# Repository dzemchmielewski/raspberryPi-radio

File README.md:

Radio for playing internet streams, with knobs, buttons, LEDs and OLED display

./software - python code
./kicad - kicad files for schematic, PCB and plexi cut out

 dzem 2024

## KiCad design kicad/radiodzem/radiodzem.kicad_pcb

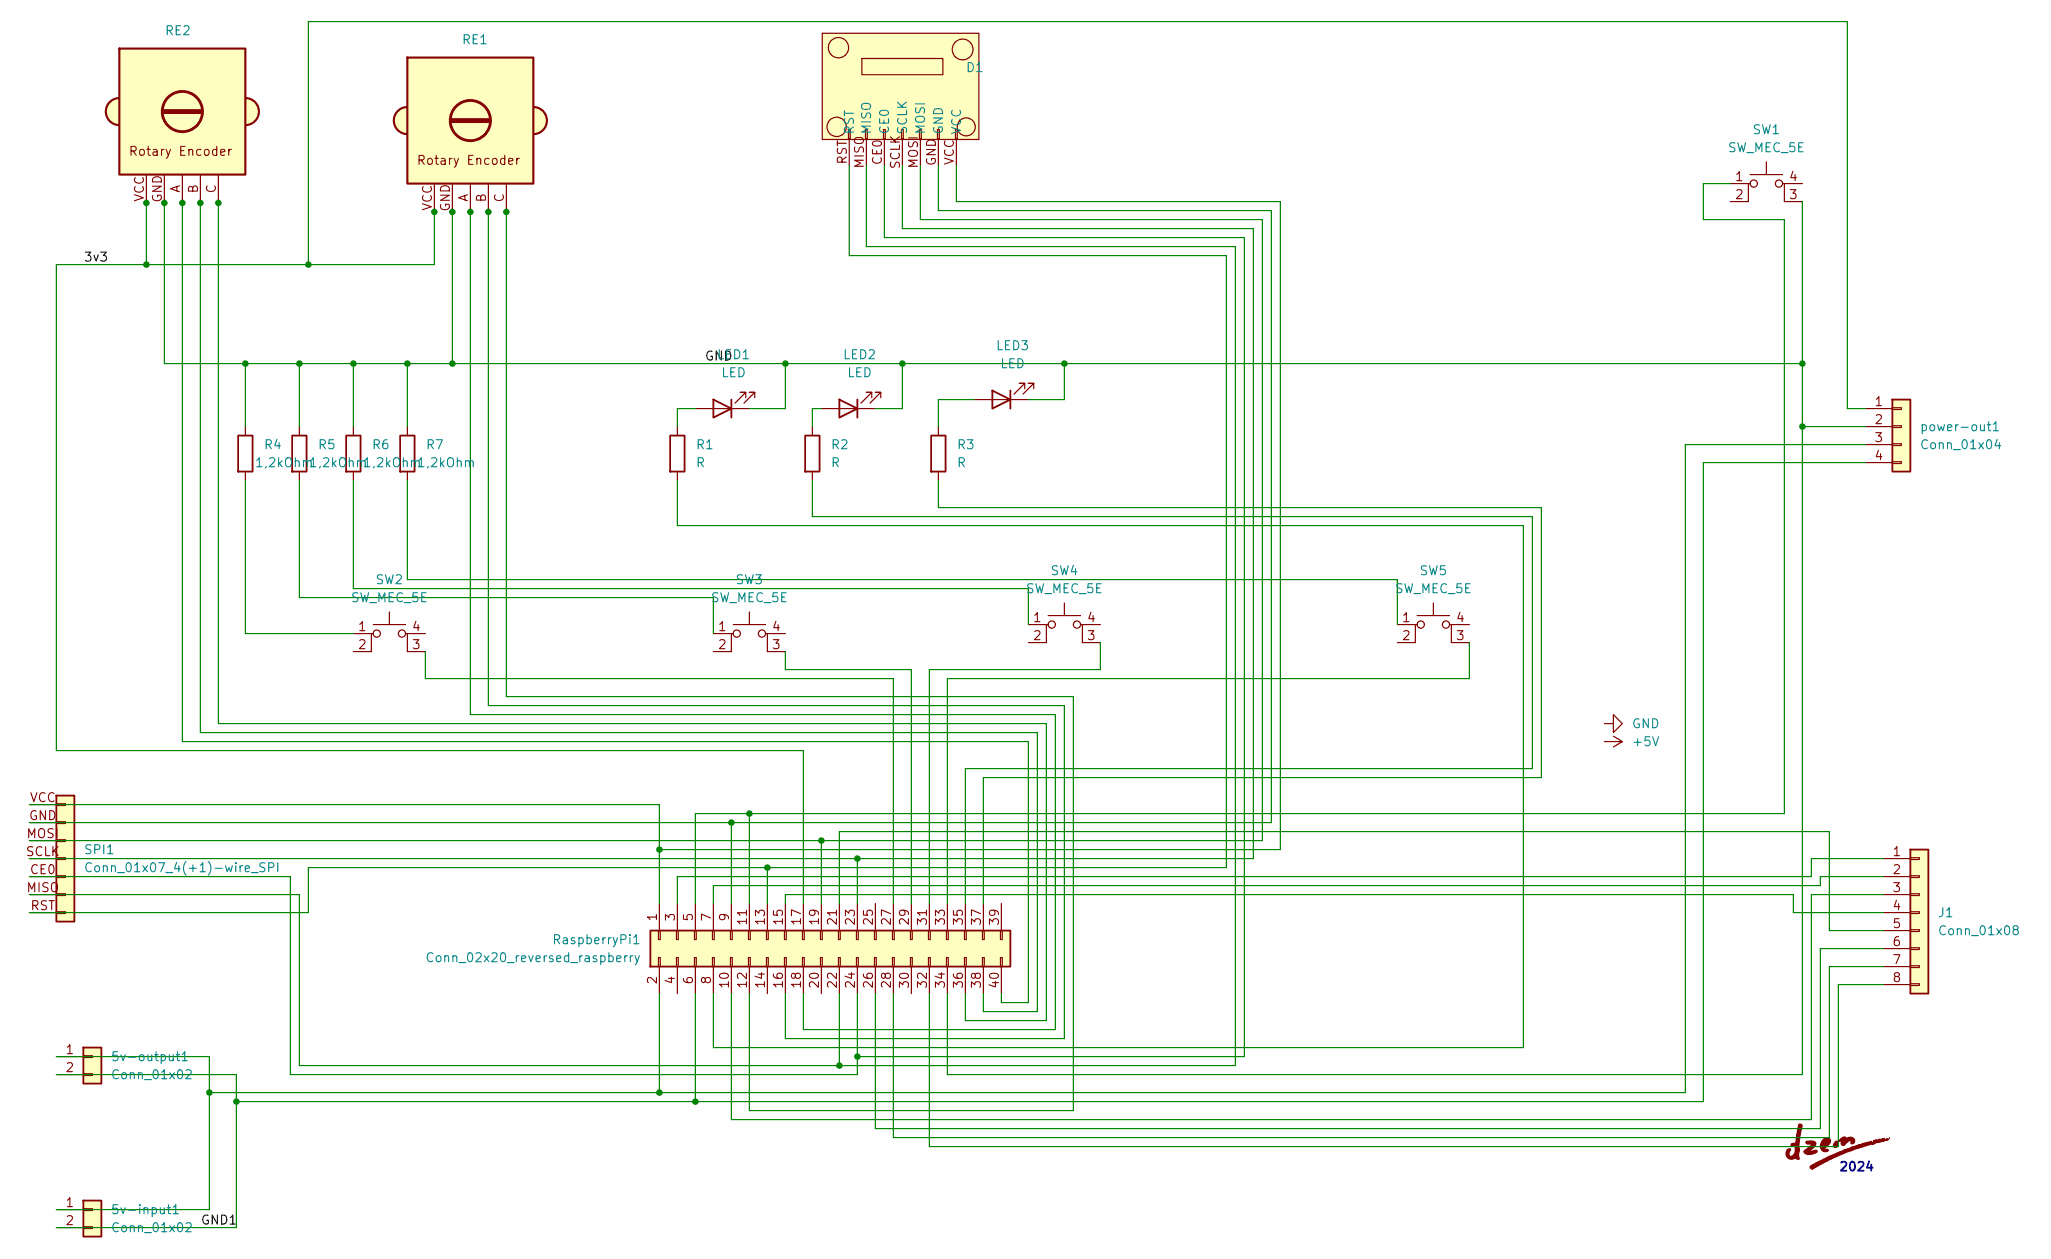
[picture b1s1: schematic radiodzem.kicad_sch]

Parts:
5v-input1: Conn_01x02; SolderWire-1sqmm_1x02_P5.4mm_D1.4mm_OD2.7mm
5v-output1: Conn_01x02; PinHeader_1x02_P2.54mm_Vertical
D1: Waveshare 1.32inch OLED Display Module
J1: Conn_01x08; PinHeader_1x08_P2.54mm_Vertical
LED1, LED2, LED3: LED; LED_D3.0mm
R1, R2, R3: R; R_Axial_DIN0207_L6.3mm_D2.5mm_P7.62mm_Horizontal
R4, R5, R6, R7: 1,2kOhm; R_Axial_DIN0207_L6.3mm_D2.5mm_P7.62mm_Horizontal
RE1, RE2: EC11 Rotary Encoder
RaspberryPi1: Conn_02x20_reversed_raspberry; PinHeader_RaspberryPi_reversed
SPI1: Conn_01x07_4(+1)-wire_SPI; PinHeader_1x07_P2.54mm_4(+1)-wire_SPI
SW1, SW2, SW3, SW4, SW5: SW_MEC_5E; SW_PUSH-12mm
power-out1: Conn_01x04; 4-pins_power_connector

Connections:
/3v3: RE1.VCC, RE2.VCC, RaspberryPi1.17, power-out1.1
/GND1: 5v-input1.2, 5v-output1.2, RaspberryPi1.6, power-out1.4
GND: LED1.1 (K), LED2.1 (K), LED3.1 (K), R4.1, R5.1, R6.1, R7.1, RE1.GND, RE2.GND, RaspberryPi1.34, SW1.3 (K), power-out1.2
unnamed: 5v-input1.1, 5v-output1.1, RaspberryPi1.2, power-out1.3
unnamed: J1.1, RaspberryPi1.3
unnamed: J1.2, RaspberryPi1.7
unnamed: J1.3, RaspberryPi1.10
unnamed: J1.4, RaspberryPi1.15
unnamed: J1.5, RaspberryPi1.21
unnamed: J1.6, RaspberryPi1.26
unnamed: J1.7, RaspberryPi1.28
unnamed: J1.8, RaspberryPi1.32
unnamed: LED1.2 (A), R1.1
unnamed: LED2.2 (A), R2.1
unnamed: LED3.2 (A), R3.1
unnamed: R4.2, SW2.1
unnamed: R5.2, SW3.1
unnamed: R6.2, SW4.1
unnamed: R7.2, SW5.1
unnamed: D1.VCC, RaspberryPi1.1, SPI1.VCC
unnamed: R1.2, RaspberryPi1.8
unnamed: D1.GND, RaspberryPi1.9, SPI1.GND
unnamed: RaspberryPi1.5, RaspberryPi1.11, SW1.1
unnamed: RE1.C, RaspberryPi1.12
unnamed: D1.RST, RaspberryPi1.13, SPI1.RST
unnamed: RE1.B, RaspberryPi1.16
unnamed: RE1.A, RaspberryPi1.18
unnamed: D1.MOSI, RaspberryPi1.19, SPI1.MOSI
unnamed: D1.MISO, RaspberryPi1.22, SPI1.MISO
unnamed: D1.SCLK, RaspberryPi1.23, SPI1.SCLK
unnamed: D1.CE0, RaspberryPi1.24, SPI1.CE0
unnamed: RaspberryPi1.27, SW2.3 (K)
unnamed: RaspberryPi1.29, SW3.3 (K)
unnamed: RaspberryPi1.31, SW4.3 (K)
unnamed: RaspberryPi1.33, SW5.3 (K)
unnamed: R2.2, RaspberryPi1.35
unnamed: RE2.C, RaspberryPi1.36
unnamed: R3.2, RaspberryPi1.37
unnamed: RE2.B, RaspberryPi1.38
unnamed: RE2.A, RaspberryPi1.40

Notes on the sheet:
2024

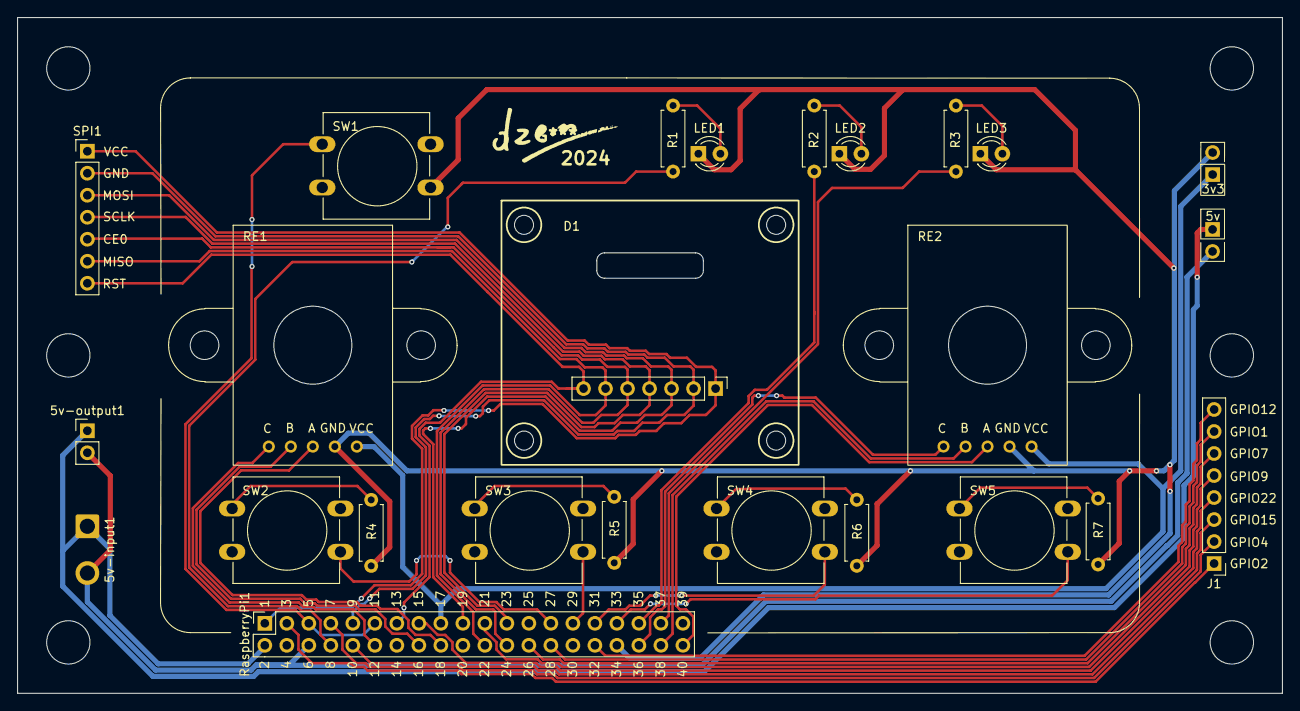
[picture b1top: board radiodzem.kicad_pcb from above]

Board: 2 copper layers, 146.0 x 78.0 mm, 24 parts (0 on the bottom side), 40 nets.

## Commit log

2024-04-05 initial refactor 1
2024-04-05 oled initial commit
2024-04-05 kicad initial commit
2024-04-10 development
2024-04-18 developemnt
2024-04-18 moon rise/set icons added
2024-04-19 Refactoring
2024-04-19 Sun & Moon info added; some other refactoring & development
2024-04-19 cache added
2024-04-20 Pin numbering adjustement
2024-04-20 Make astro info flowing through the small bottom window
2024-04-23 small fixes
2024-04-23 Refactoring - volume management
2024-04-23 Refactoring #2 - volume management
2024-04-23 Refactoring #3 - station mnagement
2024-04-23 Volume window added
2024-04-24 Minor fixes and cleaning
2024-04-24 Added persistance for runtime values
2024-04-25 Small tweaks
2024-04-25 Use gpiozero.RotaryEncoder instead of home made solution
2024-04-25 Added moon phase visualization
2024-04-25 Screensaver added
2024-04-25 Refactoring - generic display and two display devices
2024-04-26 Dummy Controller added
2024-04-27 fixes
2024-04-27 Systemd integration and some system tweaks
2024-04-27 Initialize the work on weather window
2024-04-28 Screensaver added, some tweaks
2024-04-28 configuration
2024-04-28 Some fixes & changes
2024-04-28 Stream added
2024-04-28 Snake screensaver added
2024-04-28 Refactoring - slide window added
2024-04-28 Refactoring - astro data broadcasted
2024-04-29 Meteo controller added
2024-04-29 Meteo data presenation
2024-04-29 Make red led blinking on recognize event
2024-04-29 Refactoring - led indicators
2024-04-29 Make LEDs not so bright
2024-04-29 Idea to ping phones
2024-04-30 whoishome development
2024-04-30 Description and vertical slide added
2024-04-30 Split description into two screen when is too long
2024-04-30 Wind added; slide window sleep time fixed
2024-05-01 Weird holidays added to the time window
2024-05-02 Refactoring - more Tuner to another file
2024-05-03 Changed VLC interface to be able to read Icy Metadata
2024-05-04 Added convenient window for station selection
2024-05-06 monir tweaks
2024-05-21 Some failovers added
2024-06-16 Kicad symbols & footprints moved to repository: github.com/dzemchmielewski/kicad-personal-assets
2024-08-09 Stored in memcached some radio status parameters for external readers
2024-08-11 Some radio status parameters published to external MQTT broker
2024-08-15 MQTT -retain last message
2024-08-18 MQTT retain fix; empty volume fix
2024-09-25 MQTT - live message adjustement
2024-10-22 MQQT topic name adjusted
